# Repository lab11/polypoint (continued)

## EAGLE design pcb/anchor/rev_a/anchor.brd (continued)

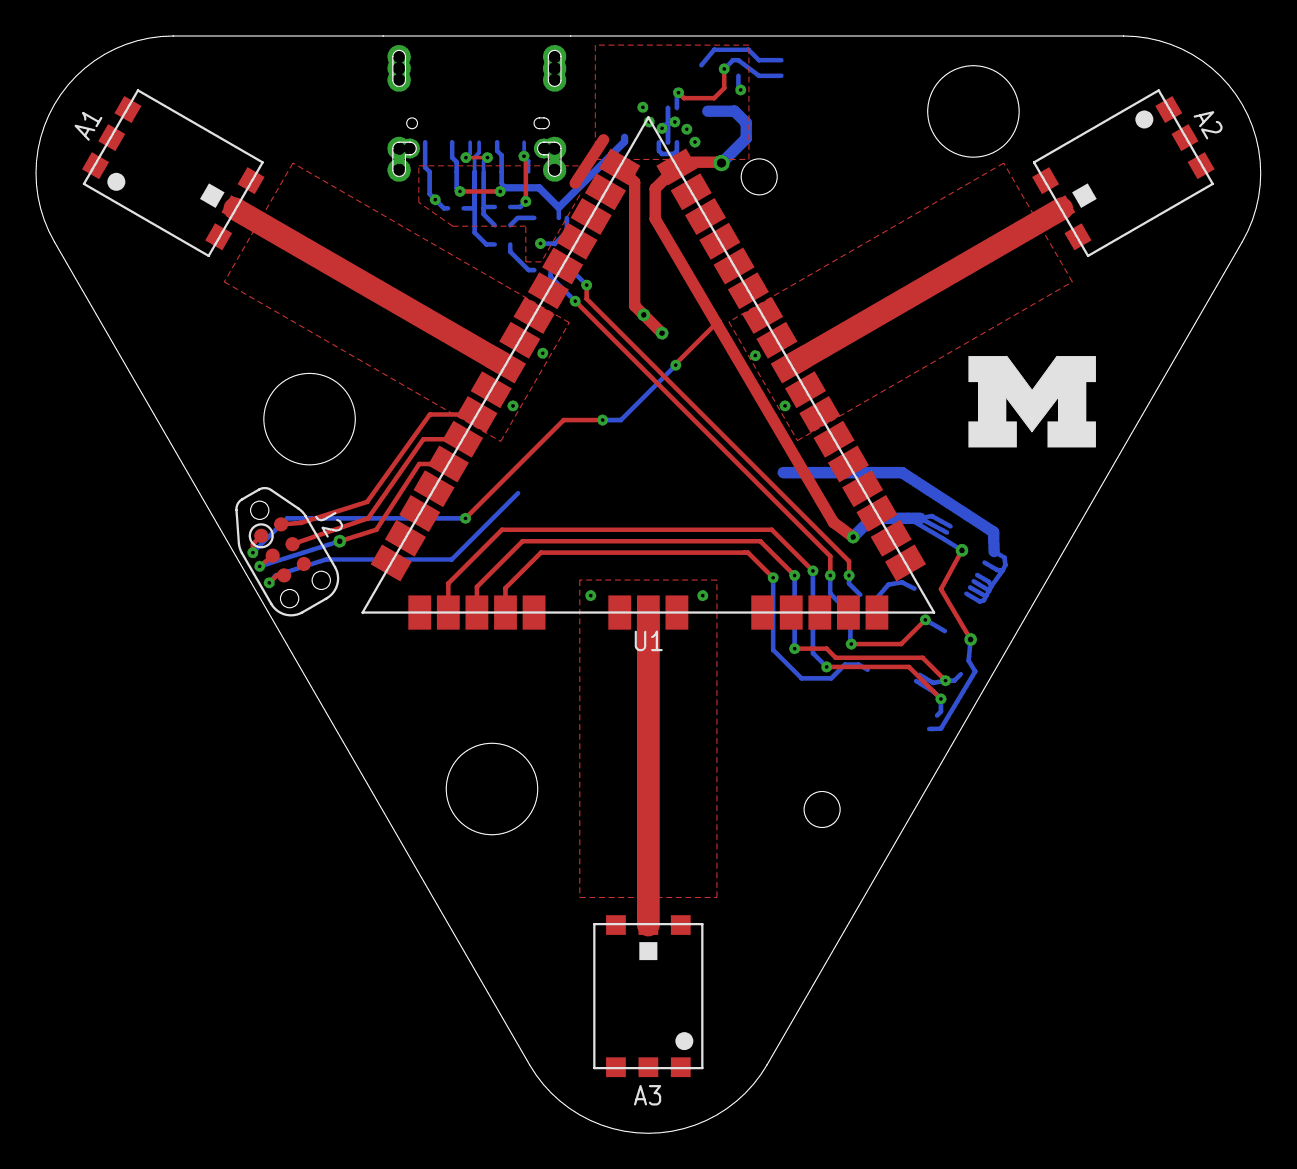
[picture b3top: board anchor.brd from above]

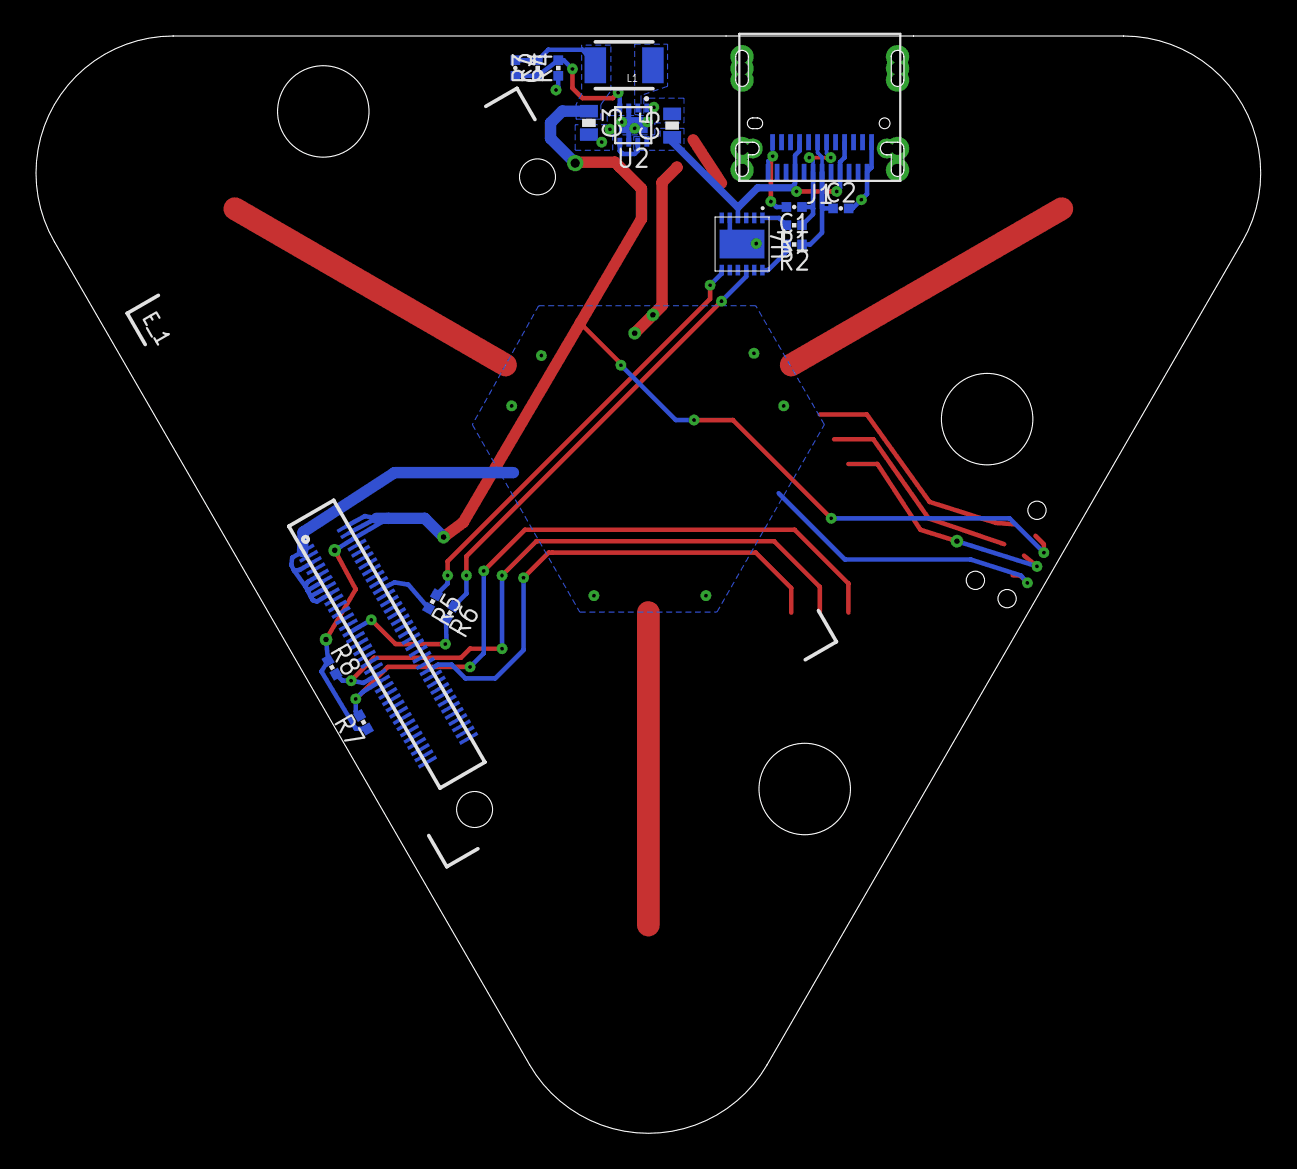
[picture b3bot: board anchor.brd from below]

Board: 2 copper layers, 68.0 x 61.0 mm, 24 parts (18 on the bottom side), 22 nets.

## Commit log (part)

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2015-09-05 testing ranging
    there is some crap in tag code for testing. should be removed when
    things work
2015-09-05 remove debugging preset in tag
2015-09-06 actually getting packets from ~20 m
2015-09-07 updated tritag mac address
2015-09-07 set EUI more properly
    make flash ID=c0:98:e5:50:50:44:50:01
2015-09-14 fix bug with sending ranges to phone
    pointers are hard
2015-09-14 updated sleep code
    added support in tag
2015-09-14 better sleep support, settings changable
    may be able to reconfigure tripoints over i2c
2015-09-14 add on-demand ranging
2015-09-16 wakeup and reset working
    hopefully we are at least kinda resilient to sleep failures.
2015-09-16 more reset loops
    try to keep these things running
2015-09-16 small clean
2015-09-16 copy data
2015-09-17 rework how i2c is handled.
    should solve the no response problem
2015-09-17 add check to make sure we don't deadlock on int
    if dw1000 gets in "interrupt all the things!" state, we can now check
    for that and reset
2015-09-18 notify and value update working with limited testing
2015-09-18 use notify feature that works now
2015-09-18 clean up dw1000.c
    add comments
    remove old functions
    remove other unused defines
2015-09-18 little better node code
2015-09-18 slight comment change
2015-09-21 cleaning up tritag app some more
2015-09-21 need to toggle wakeup pin, not just assert it
2015-09-21 update to flash
2015-09-21 Add readme for tripoint firmware
2015-09-21 clean up delay files
2015-09-21 changes have been incorporated
2015-09-21 update readme with hardware and software
2015-09-22 reformatting .h files
    more logical
2015-09-22 update nrf5x base
2015-09-22 rename pcb files
2015-09-22 adding hw start
2015-09-22 get rid of interrupt every 5 ms
2015-09-22 another attempt to get sleep working
    no luck
2015-09-23 refactor code layout for multiple apps
    also start on calibration
    fingers crossed things still work
2015-09-23 adding gerbers for calibration brace
2015-09-23 update hardware readme
2015-09-23 add readme for tritag ble app
2015-09-23 fix issue with state machine
    reset works
2015-09-23 calibration algorithm first pass
2015-09-24 calibration seems plausible
2015-09-24 Add calibration design
2015-09-24 updated calib with 4 pkt protocol
2015-09-26 configure tritag addresses
2015-09-27 fixed array bounds issue
    reformatted notification packet
2015-09-28 slight cleanup
2015-09-28 update doc to typable characters
    colors dont make good column headers
2015-09-28 update API to what the calibration node sends back
2015-09-28 add sample data
2015-09-28 add readme for calibration
2015-09-28 no compiler warnings
2015-09-28 update some old code in nrf folder
2015-09-28 more text in api
2015-09-28 First pass at revised calibration
    Precision across many clock domains is tricky..
2015-09-29 fixing broken submodule
2015-09-29 first pass at YET ANOTHER CALIBRATION SCHEME
2015-09-29 Also add pdf of diagram
2015-09-29 update calibration script
2015-09-29 added function for calibration
    and the correct places to add the offsets
2015-09-30 fix issue with javascript numbers over 32 bit
2015-09-30 working code to test backscatter
2015-09-30 add more sample calib data
2015-09-30 update calibration doc
2015-10-01 put led back on tag
2015-10-01 update to magic check softdevice version
2015-10-01 cases
2015-10-01 move 3d models into better folders
2015-10-01 rename case to something reasonable
2015-10-01 update case links after moves
2015-10-01 updated breakout
2015-10-02 update eddystone url
2015-10-02 some hope of cordova app working
2015-10-02 add readme
2015-10-02 getting ranges notified
2015-10-03 added adv code
2015-10-03 little more cleaning on summon app
2015-10-03 getting closer to summon app extracting data
    native javascript buffer handling is awful. Give me node!
2015-10-05 breakout basically done
2015-10-05 Finish calibration script. Closes #4.
2015-10-05 calibration values over host interface
2015-10-05 Update a single calibration file
2015-10-05 check for -1 in calib data
2015-10-05 create readme for firmware folder
2015-10-05 comment in makefile
2015-10-05 remove fake calibration from code
2015-10-05 save calibration value
2015-10-06 Re-fix calibration
2015-10-06 Fix new node bug
2015-10-06 Remove unnecessary branch
2015-10-06 changes
    sorry about the commit message
2015-10-07 Set calibration distance to rig mode instead of desk mode
2015-10-07 changed print
2015-10-07 updated calib data
2015-10-07 summon app doesnt look as terrible
2015-10-08 add polypoint logo -brad
2015-10-09 fixed with new summon version
2015-10-10 bad changes to calibration log
2015-10-10 more calib data
2015-10-10 add meta
2015-10-10 bounds check in calibration
2015-10-12 update calibration folder
2015-10-12 update main readme
2015-10-13 fixing buffer overflow issue with ble notification
2015-10-13 code changes from backscatter testing
2015-10-19 added docs for tridev pcb
2015-10-20 updated pcb with different pours
2015-10-22 adding latest gerbers
2015-10-23 ui change to tridev
2015-10-23 added python script for talking to tripoint
2015-10-23 rev b of the breakout
2015-10-23 rounding corner of only 45 degree rf trace
2015-10-24 revert tridev to version that was fabbed
2015-10-26 updated i2c ftdi code
2015-11-02 accidentally committed bad code earlier
2015-11-02 actually adding CIR extraction logic this time
2015-11-10 no great results
2015-11-19 update tritag to new make system
2015-11-19 small changes to v1p2 board (cosmetic)
2015-11-20 little doc on tritag-anchor
2015-11-20 add some doc about node code
2015-11-23 add tridev note
2015-12-02 backscatter CIR is looking better
2015-12-08 wired clock sync seems to be showing promise
2015-12-08 modifying code to work with longer recordings at higher fidelity
2015-12-11 Adding operating system dependencies
2016-01-08 latest un-committed changes
2016-01-12 modifications to support bandstitching
2016-01-14 Updated to new nrf5x-base service API
2016-02-01 adding bandstitching analysis code
2016-02-10 new sanity checks in makefiles
2016-02-10 Move DEVICE_NAME #define to fix duplicate #defines
2016-02-13 An improvement upon PolyPoint's previous localization consistency and performance. First, waking DW1000 from sleep greatly hinders its immediate RX performance, so all DW1000 sleep code has been remo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
2016-02-18 uncommitted changes resulting in correct bandstitching functionality
2016-02-18 first attempt at adding uart functionality to bandstitching code
2016-02-18 up to maximum baudrate attainable (6 Mbps)
2016-02-19 adding new schematic components for timebase board
2016-02-20 working on timebase schematic. Jitter cleaner is the only thing left to include
2016-02-21 adding adapter board to test PinPoint with TriDev board
2016-02-21 minor cosmetic fixes
2016-02-21 adding gerbers for pinpoint timebase and pinpoint to tridev adapter baord
2016-02-22 adding BOMs for two PinPoint boards
2016-02-24 scripts and code for performing calibration over saleae
2016-02-24 starting from scratch with calibration data
2016-02-24 created script to process saleae traces and convert to calibration measurements
2016-02-25 a couple typos with the calibration code
2016-02-25 typo in using calibration data
2016-03-03 working UART DMA offload
2016-03-04 Fix trivial warnings in calibration.c
2016-03-04 Add header/footer to uart packets
2016-03-04 Add initial dump script
2016-03-04 Wrap whole thing in keyboardinterrupt try/except
2016-03-04 Add binary output support
2016-03-04 Report round_num; actually check footer
2016-03-04 adding rxpacc and finfo reads
2016-03-11 positive results with out_manchester_works.bin
2016-03-12 now modified to work at faster update rate (out_manchester_fast_works.bin)
2016-03-16 good results with monostatic radar setup
2016-03-22 minor modifications to support multiple antennas
2016-03-22 updating dw1000-driver
2016-03-26 fixing bugs introduced from migrating to scratchspace utilization
2016-03-26 adding candidate code for reduced bitrate, long-range code
2016-03-26 candidate code to test smarter response window sizing
2016-03-26 fixing a couple mistakes in git master rebase
2016-03-27 reliable code for low datarate, need to test for higher baud rates now
2016-03-27 fast baudrate now works as well
2016-03-27 adding UART capability
2016-03-29 adding CW test mode capability
2016-04-02 adding newly-calibrated tags
2016-04-02 master kicks off sync packets as expected
2016-04-02 initial code to test out glossy
2016-04-02 glossy achieves time sync
2016-04-02 getting closer to LPM working
2016-04-02 getting rid of depth field in sync flood
2016-04-02 Glossy PER tests are now complete
2016-04-02 fixing transmit counter overflow issues
2016-04-02 LWB appears to work!
2016-04-02 fixing ack bugs in anchor response windows
2016-04-02 finishing up tag code to do schedule requests
2016-04-03 we were past the program memory limit. got rid of calibration app which currently is not used anymroe
2016-04-03 everything seems to be in a stable enough state to start testing
2016-04-03 candidate fix for timestamp overflow issues
2016-04-03 adding code which correctly reads in uart logging output
2016-04-03 getting close with octave code
2016-04-03 overflow issue
2016-04-04 real rxoverrun issue fixed
2016-04-05 changes for doing glossy atrium tests
2016-04-05 adding new python script which interprets new glossy output data stream
2016-04-05 done with porting ranging to python
2016-04-06 bug in re-initialization of anchor after a glossy sync
2016-04-06 WIP: ranging calculation seems to be working
2016-04-06 don't die on bad range
2016-04-06 small stability changes
2016-04-06 Only locate if asked
2016-04-06 Add PID option to short set ID
2016-04-06 better anchor listening code
2016-04-06 Add anchor loc to outfile
2016-04-06 Add newline
2016-04-07 Use decawave for timestamps
2016-04-07 implement recursive iteration
2016-04-07 fixing lots of bugs that were plaguing polypoint tests
2016-04-08 Add anchor history; guly but effective
2016-04-08 Skip useless processing; add calibration
2016-04-09 adding channel model simulation
2016-04-10 channel index miscalculation
2016-04-10 new uart offload code
2016-04-20 adding PPS sync logic
2016-08-26 [old changes on disk]: Add diversity flag
2016-08-31 off-by-one in clock offset calculation
2016-09-01 fixing reliability issues in scheduleing and crystal offset compensation
2016-09-03 getting closer to correct glossy measurements, just need to incorporate real calibration data
2016-09-03 down to 16k offset.... almost there
2016-09-07 final sync code
2016-09-09 adding readme for calibration procedure
2016-09-15 fixing compilation errors
2016-09-16 adding flooding ranges back to master
2016-09-16 timer fixes that should be merged into master
2016-09-20 should use double buffer operation all the time
2016-09-20 bad to re-enable rx during rxcallback for some reason...
2016-09-20 make sure everyone is flooding on the correct channel
2016-09-23 avoid resetting anchor before flood is complete
2016-09-23 adding reporting code
2016-09-26 schedule issues when left on between master power cycles
2016-09-27 a bit better stability. Overruns not always caught though...
2016-09-29 better reliability. Still not quite there...
2016-10-03 reliability approaching nominal
2016-10-11 Add screenshot of app
2016-10-11 Add app screenshot
2016-10-13 Add test data script
2016-10-19 code used for IPSN submission
2016-10-20 python script seems to now work correctly. oct2py still giving errors though
2016-10-20 Add GDP POST to summon; add z to GDP packet
2016-10-23 (untested) pull anchor locations dynamically
2016-10-23 demo with looping history
2016-10-23 formatting anchor locations as JSON
2016-10-24 Update data_dump_glossy with attempt at GDP support
2017-02-08 Release under the Apache 2.0 License
    License terms confirmed with @bradjc and @bpkempke.
